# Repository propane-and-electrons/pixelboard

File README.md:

pixelboard
----------

WS2812 RGB LED arrays in a variety of sizes.

Very similar to the [Adafruit Neopixel](http://learn.adafruit.com/adafruit-neopixel-uberguide) boards developed at around the same time. I need a marketing team and more time to make more board variants.

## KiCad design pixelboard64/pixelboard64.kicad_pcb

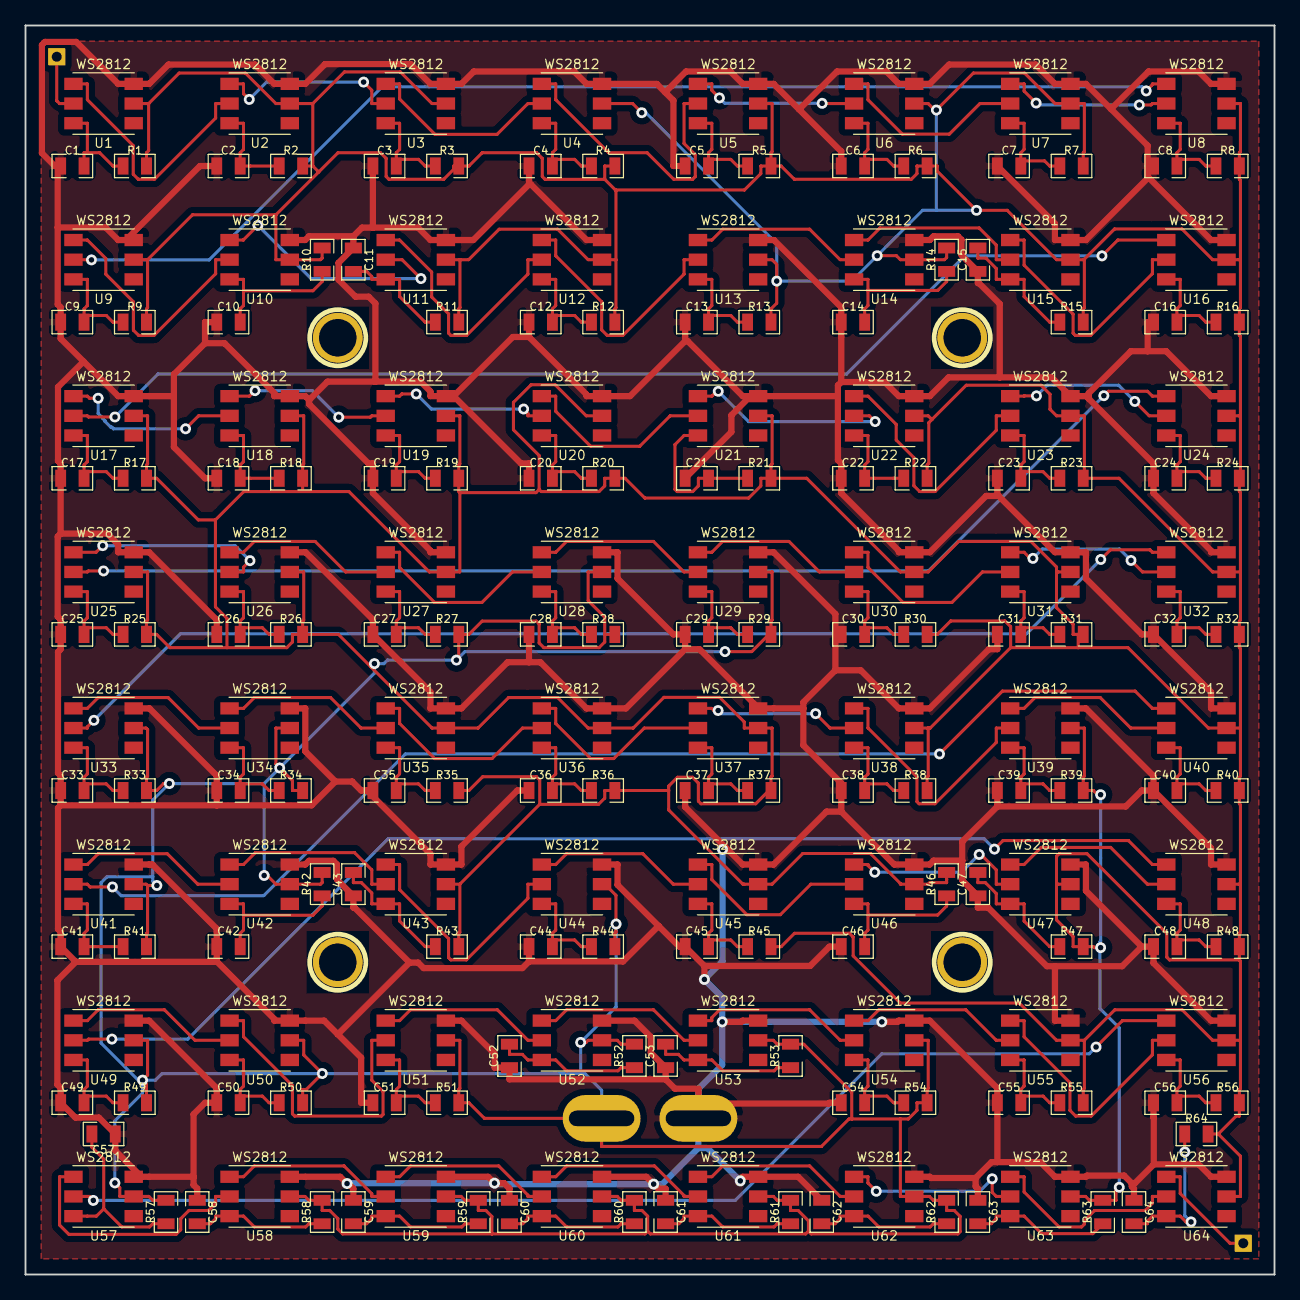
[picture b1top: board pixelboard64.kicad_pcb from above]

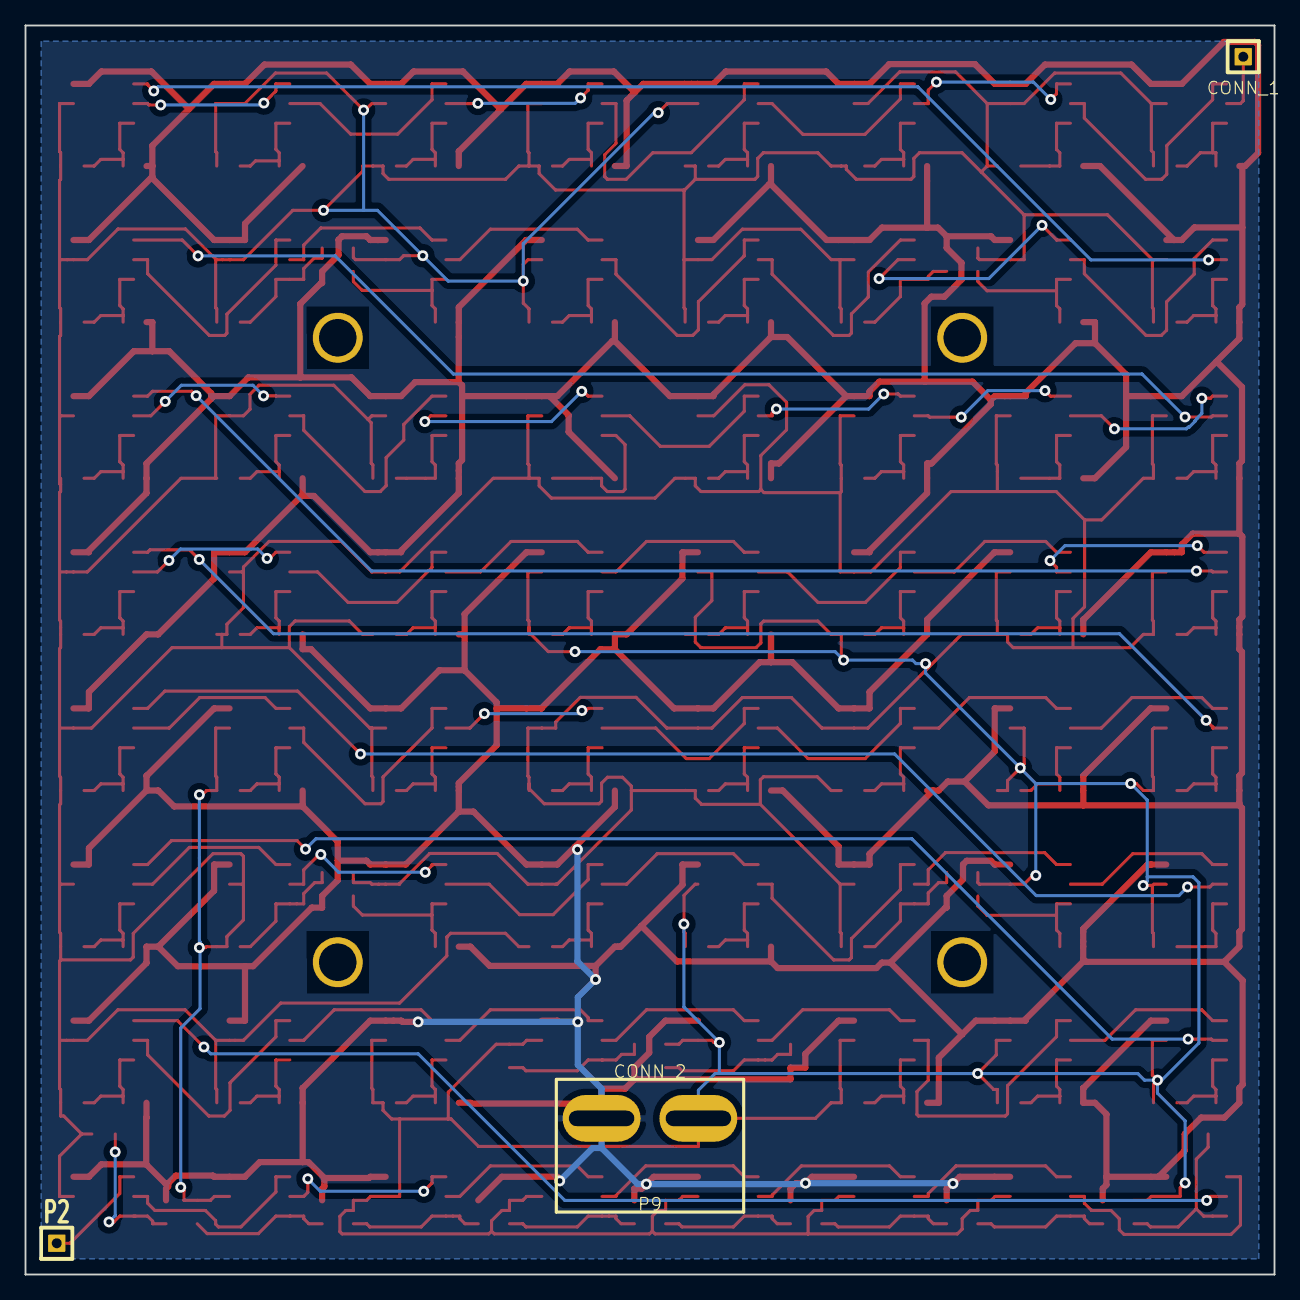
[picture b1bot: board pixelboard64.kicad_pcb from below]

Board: 2 copper layers, 101.6 x 101.6 mm, 199 parts (3 on the bottom side), 131 nets.

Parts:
C1, C2, C3, C4, C5, C6, C7, C8, C9, C10, C11, C12, C13, C14, C15, C16, C17, C18, C19, C20, C21, C22, C23, C24, C25, C26, C27, C28, C29, C30, C31, C32, C33, C34, C35, C36, C37, C38, C39, C40, C41, C42, C43, C44, C45, C46, C47, C48, C49, C50, C51, C52, C53, C54, C55, C56, C57, C58, C59, C60, C61, C62, C63, C64: 0.1uF; SM0805
H1, H2, H3, H4: SCREWHOLE; 1pin
P1, P2: CONN_1; SIL-1
P9: CONN_2; POWERPOLE-2H
R1, R2, R3, R4, R5, R6, R7, R8, R9, R10, R11, R12, R13, R14, R15, R16, R17, R18, R19, R20, R21, R22, R23, R24, R25, R26, R27, R28, R29, R30, R31, R32, R33, R34, R35, R36, R37, R38, R39, R40, R41, R42, R43, R44, R45, R46, R47, R48, R49, R50, R51, R52, R53, R54, R55, R56, R57, R58, R59, R60, R61, R62, R63, R64: 150R; SM0805
U1, U2, U3, U4, U5, U6, U7, U8, U9, U10, U11, U12, U13, U14, U15, U16, U17, U18, U19, U20, U21, U22, U23, U24, U25, U26, U27, U28, U29, U30, U31, U32, U33, U34, U35, U36, U37, U38, U39, U40, U41, U42, U43, U44, U45, U46, U47, U48, U49, U50, U51, U52, U53, U54, U55, U56, U57, U58, U59, U60, U61, U62, U63, U64: WS2812; 5050

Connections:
+5V: P9.2, R1.2, R2.2, R3.2, R4.2, R5.2, R6.2, R7.2, R8.2, R9.2, R10.2, R11.2, R12.2, R13.2, R14.2, R15.2, R16.2, R17.2, R18.2, R19.2, R20.2, R21.2, R22.2, R23.2, R24.2, R25.2, R26.2, R27.2, R28.2, R29.2, R30.2, R31.2, R32.2, R33.2, R34.2, R35.2, R36.2, R37.2, R38.2, R39.2, R40.2, R41.2, R42.2, R43.2, R44.2, R45.2, R46.2, R47.2, R48.2, R49.2, R50.2, R51.2, R52.2, R53.2, R54.2, R55.2, R56.2, R57.2, R58.2, R59.2, R60.2, R61.2, R62.2, R63.2, R64.2, U1.5, U2.5, U3.5, U4.5, U5.5, U6.5, U7.5, U8.5, U9.5, U10.5, U11.5, U12.5, U13.5, U14.5, U15.5, U16.5, U17.5, U18.5, U19.5, U20.5, U21.5, U22.5, U23.5, U24.5, U25.5, U26.5, U27.5, U28.5, U29.5, U30.5, U31.5, U32.5, U33.5, U34.5, U35.5, U36.5, U37.5, U38.5, U39.5, U40.5, U41.5, U42.5, U43.5, U44.5, U45.5, U46.5, U47.5, U48.5, U49.5, U50.5, U51.5, U52.5, U53.5, U54.5, U55.5, U56.5, U57.5, U58.5, U59.5, U60.5, U61.5, U62.5, U63.5, U64.5
/DIN: P1.1, U1.2
/DOUT: P2.1, U64.1
GND: C1.1, C2.1, C3.1, C4.1, C5.1, C6.1, C7.1, C8.1, C9.1, C10.1, C11.1, C12.1, C13.1, C14.1, C15.1, C16.1, C17.1, C18.1, C19.1, C20.1, C21.1, C22.1, C23.1, C24.1, C25.1, C26.1, C27.1, C28.1, C29.1, C30.1, C31.1, C32.1, C33.1, C34.1, C35.1, C36.1, C37.1, C38.1, C39.1, C40.1, C41.1, C42.1, C43.1, C44.1, C45.1, C46.1, C47.1, C48.1, C49.1, C50.1, C51.1, C52.1, C53.1, C54.1, C55.1, C56.1, C57.1, C58.1, C59.1, C60.1, C61.1, C62.1, C63.1, C64.1, P9.1, U1.6, U2.6, U3.6, U4.6, U5.6, U6.6, U7.6, U8.6, U9.6, U10.6, U11.6, U12.6, U13.6, U14.6, U15.6, U16.6, U17.6, U18.6, U19.6, U20.6, U21.6, U22.6, U23.6, U24.6, U25.6, U26.6, U27.6, U28.6, U29.6, U30.6, U31.6, U32.6, U33.6, U34.6, U35.6, U36.6, U37.6, U38.6, U39.6, U40.6, U41.6, U42.6, U43.6, U44.6, U45.6, U46.6, U47.6, U48.6, U49.6, U50.6, U51.6, U52.6, U53.6, U54.6, U55.6, U56.6, U57.6, U58.6, U59.6, U60.6, U61.6, U62.6, U63.6, U64.6
unnamed: C47.2, R47.1, U47.3
unnamed: U49.1, U50.2
unnamed: C50.2, R50.1, U50.3
unnamed: C46.2, R46.1, U46.3
unnamed: C48.2, R48.1, U48.3
unnamed: U47.1, U48.2
unnamed: U48.1, U49.2
unnamed: C45.2, R45.1, U45.3
unnamed: C54.2, R54.1, U54.3
unnamed: U54.1, U55.2
unnamed: C51.2, R51.1, U51.3
unnamed: C53.2, R53.1, U53.3
unnamed: U53.1, U54.2
unnamed: C49.2, R49.1, U49.3
unnamed: U52.1, U53.2
unnamed: C52.2, R52.1, U52.3
unnamed: U50.1, U51.2
unnamed: U51.1, U52.2
unnamed: C40.2, R40.1, U40.3
unnamed: U39.1, U40.2
unnamed: C39.2, R39.1, U39.3
unnamed: C38.2, R38.1, U38.3
unnamed: U38.1, U39.2
unnamed: C37.2, R37.1, U37.3
unnamed: U36.1, U37.2
unnamed: U37.1, U38.2
unnamed: C43.2, R43.1, U43.3
unnamed: U42.1, U43.2
unnamed: C44.2, R44.1, U44.3
unnamed: U45.1, U46.2
unnamed: U46.1, U47.2
unnamed: C42.2, R42.1, U42.3
unnamed: C41.2, R41.1, U41.3
unnamed: U40.1, U41.2
unnamed: U41.1, U42.2
unnamed: U43.1, U44.2
unnamed: U44.1, U45.2
unnamed: U57.1, U58.2
unnamed: U58.1, U59.2
unnamed: U59.1, U60.2
unnamed: U60.1, U61.2
unnamed: U61.1, U62.2
unnamed: U62.1, U63.2
unnamed: U63.1, U64.2
unnamed: U55.1, U56.2
unnamed: U35.1, U36.2
unnamed: U34.1, U35.2
unnamed: U33.1, U34.2
unnamed: U32.1, U33.2
unnamed: U25.1, U26.2
unnamed: U24.1, U25.2
unnamed: U16.1, U17.2
unnamed: U8.1, U9.2
unnamed: C63.2, R63.1, U63.3
unnamed: C64.2, R64.1, U64.3
unnamed: U7.1, U8.2
unnamed: U9.1, U10.2
unnamed: U17.1, U18.2
unnamed: U18.1, U19.2
unnamed: U10.1, U11.2
unnamed: U19.1, U20.2
unnamed: U11.1, U12.2
unnamed: U20.1, U21.2
unnamed: U21.1, U22.2
unnamed: U22.1, U23.2
unnamed: U23.1, U24.2
unnamed: U12.1, U13.2
unnamed: U13.1, U14.2
unnamed: U14.1, U15.2
unnamed: U15.1, U16.2
unnamed: U6.1, U7.2
unnamed: U5.1, U6.2
unnamed: U4.1, U5.2
unnamed: U3.1, U4.2
unnamed: U2.1, U3.2
unnamed: U1.1, U2.2
unnamed: U31.1, U32.2
unnamed: U30.1, U31.2
unnamed: U29.1, U30.2
unnamed: U28.1, U29.2
unnamed: U27.1, U28.2
unnamed: U26.1, U27.2
unnamed: U56.1, U57.2
unnamed: C58.2, R58.1, U58.3
unnamed: C57.2, R57.1, U57.3
unnamed: C55.2, R55.1, U55.3
unnamed: C56.2, R56.1, U56.3
unnamed: C61.2, R61.1, U61.3
unnamed: C62.2, R62.1, U62.3
unnamed: C60.2, R60.1, U60.3
unnamed: C59.2, R59.1, U59.3
unnamed: C35.2, R35.1, U35.3
unnamed: C11.2, R11.1, U11.3
unnamed: C14.2, R14.1, U14.3
unnamed: C13.2, R13.1, U13.3
unnamed: C9.2, R9.1, U9.3
unnamed: C12.2, R12.1, U12.3
unnamed: C17.2, R17.1, U17.3
unnamed: C18.2, R18.1, U18.3
unnamed: C16.2, R16.1, U16.3
unnamed: C15.2, R15.1, U15.3
unnamed: C4.2, R4.1, U4.3
unnamed: C3.2, R3.1, U3.3
unnamed: C6.2, R6.1, U6.3
unnamed: C2.2, R2.1, U2.3
unnamed: C1.2, R1.1, U1.3
unnamed: C8.2, R8.1, U8.3
unnamed: C10.2, R10.1, U10.3
unnamed: C7.2, R7.1, U7.3
unnamed: C5.2, R5.1, U5.3
unnamed: C29.2, R29.1, U29.3
unnamed: C32.2, R32.1, U32.3
unnamed: C27.2, R27.1, U27.3
unnamed: C30.2, R30.1, U30.3
unnamed: C31.2, R31.1, U31.3
unnamed: C36.2, R36.1, U36.3
unnamed: C33.2, R33.1, U33.3
unnamed: C34.2, R34.1, U34.3
unnamed: C22.2, R22.1, U22.3
unnamed: C24.2, R24.1, U24.3
unnamed: C21.2, R21.1, U21.3
unnamed: C20.2, R20.1, U20.3
unnamed: C19.2, R19.1, U19.3
unnamed: C26.2, R26.1, U26.3
unnamed: C28.2, R28.1, U28.3
unnamed: C25.2, R25.1, U25.3
unnamed: C23.2, R23.1, U23.3

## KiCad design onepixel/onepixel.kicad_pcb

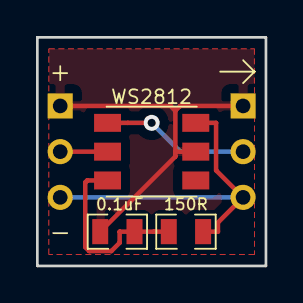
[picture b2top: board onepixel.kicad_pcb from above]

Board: 2 copper layers, 12.7 x 12.7 mm, 5 parts (0 on the bottom side), 5 nets.

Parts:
C1: 0.1uF; SM0805
P1: IN; SIL-3
P2: OUT; SIL-3
R1: 150R; SM0805
U1: WS2812; 5050

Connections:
/DIN: P1.2, U1.2
/DOUT: P2.2, U1.1
GND: C1.1, P1.3, P2.3, U1.6
unnamed: C1.2, R1.1, U1.3
VCC: P1.1, P2.1, R1.2, U1.5

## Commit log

2013-04-20 initial commit of onepixel
2013-04-22 adding pixelboard64
2013-04-30 adding polarity indicator, using older format
2013-04-30 changing to old version
2013-10-19 labels reversed
2013-10-19 moving the via a little bit
2014-01-05 adding readme
